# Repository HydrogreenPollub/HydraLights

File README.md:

View this project on [CADLAB.io](https://cadlab.io/project/29338). 

# HydraLights

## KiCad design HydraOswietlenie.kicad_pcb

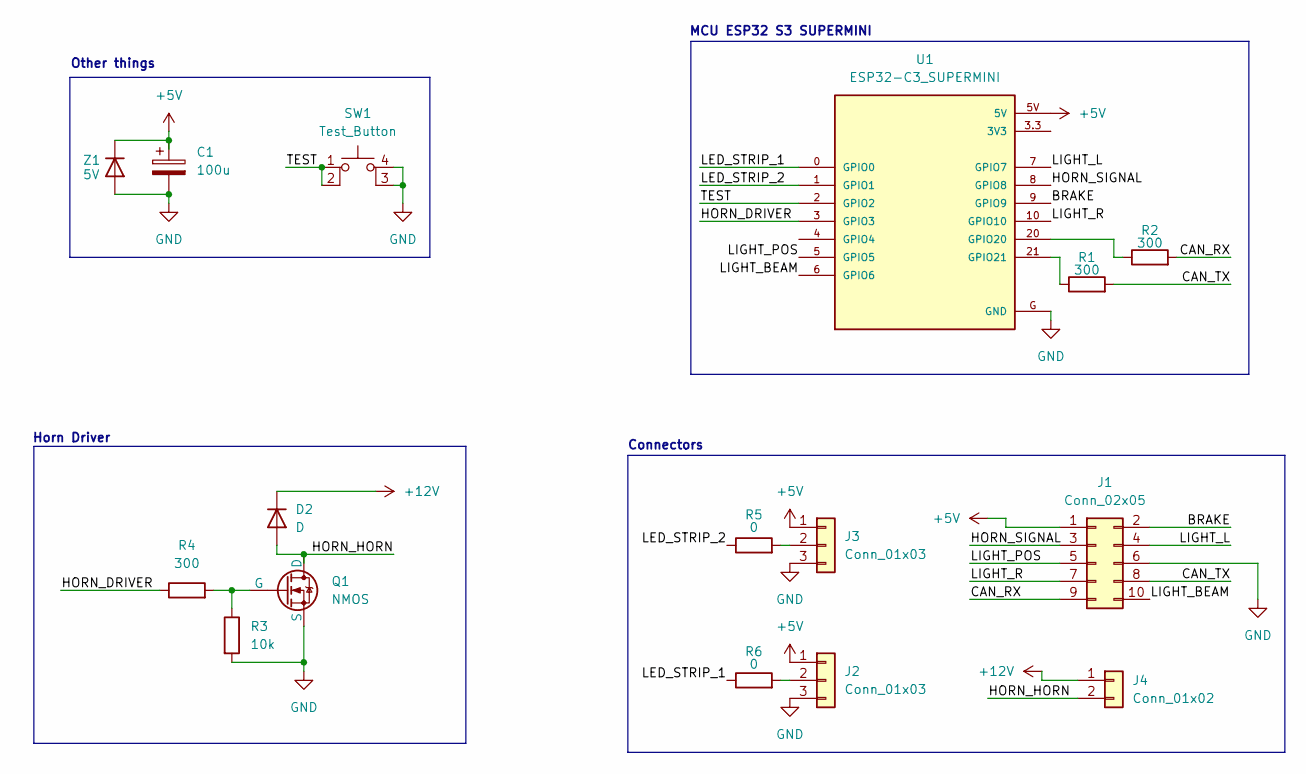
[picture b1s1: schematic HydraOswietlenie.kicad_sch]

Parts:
C1: 100u; CP_Radial_D10.0mm_P5.00mm
D2: D; D_DO-41_SOD81_P10.16mm_Horizontal
J1: Conn_02x05; Molex_Mini-Fit_Jr_5569-10A1_2x05_P4.20mm_Horizontal
J2, J3: Conn_01x03; 39303035
J4: Conn_01x02; Molex_Mini-Fit_Jr_5569-02A2_2x01_P4.20mm_Horizontal
Q1: NMOS; TO546P1558X498X2499-3
R1, R2, R4: 300; R_Axial_DIN0207_L6.3mm_D2.5mm_P7.62mm_Horizontal
R3: 10k; R_Axial_DIN0207_L6.3mm_D2.5mm_P7.62mm_Horizontal
R5, R6: 0; R_Axial_DIN0207_L6.3mm_D2.5mm_P7.62mm_Horizontal
SW1: Test_Button; TL3305BF160QG
U1: ESP32-C3_SUPERMINI; MODULE_ESP32-C3_SUPERMINI
Z1: 5V; D_DO-41_SOD81_P10.16mm_Horizontal

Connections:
+5V: C1.1, J1.1, J2.1, J3.1, U1.5V, Z1.1 (K)
+12V: D2.1 (K), J4.1
/BRAKE: J1.2, U1.9 (GPIO9)
/CAN_RX: J1.9, R2.2
/CAN_TX: J1.8, R1.2
/HORN_DRIVER: R4.1, U1.3 (GPIO3)
/HORN_HORN: D2.2 (A), J4.2, Q1.1 (D)
/HORN_SIGNAL: J1.3, U1.8 (GPIO8)
/LED_STRIP_1: R6.1, U1.0 (GPIO0)
/LED_STRIP_2: R5.1, U1.1 (GPIO1)
/LIGHT_BEAM: J1.10, U1.6 (GPIO6)
/LIGHT_L: J1.4, U1.7 (GPIO7)
/LIGHT_POS: J1.5, U1.5 (GPIO5)
/LIGHT_R: J1.7, U1.10 (GPIO10)
/TEST: SW1.1, SW1.2, U1.2 (GPIO2)
GND: C1.2, J1.6, J2.3, J3.3, Q1.3 (S), R3.2, SW1.3 (K), SW1.4 (A), U1.G (GND), Z1.2 (A); also elsewhere on the board
unnamed: J2.2, R6.2
unnamed: J3.2, R5.2
unnamed: Q1.2 (G), R3.1, R4.2
unnamed: R2.1, U1.20 (GPIO20)
unnamed: R1.1, U1.21 (GPIO21)

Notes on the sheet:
Horn Driver
Other things
MCU ESP32 S3 SUPERMINI
Connectors

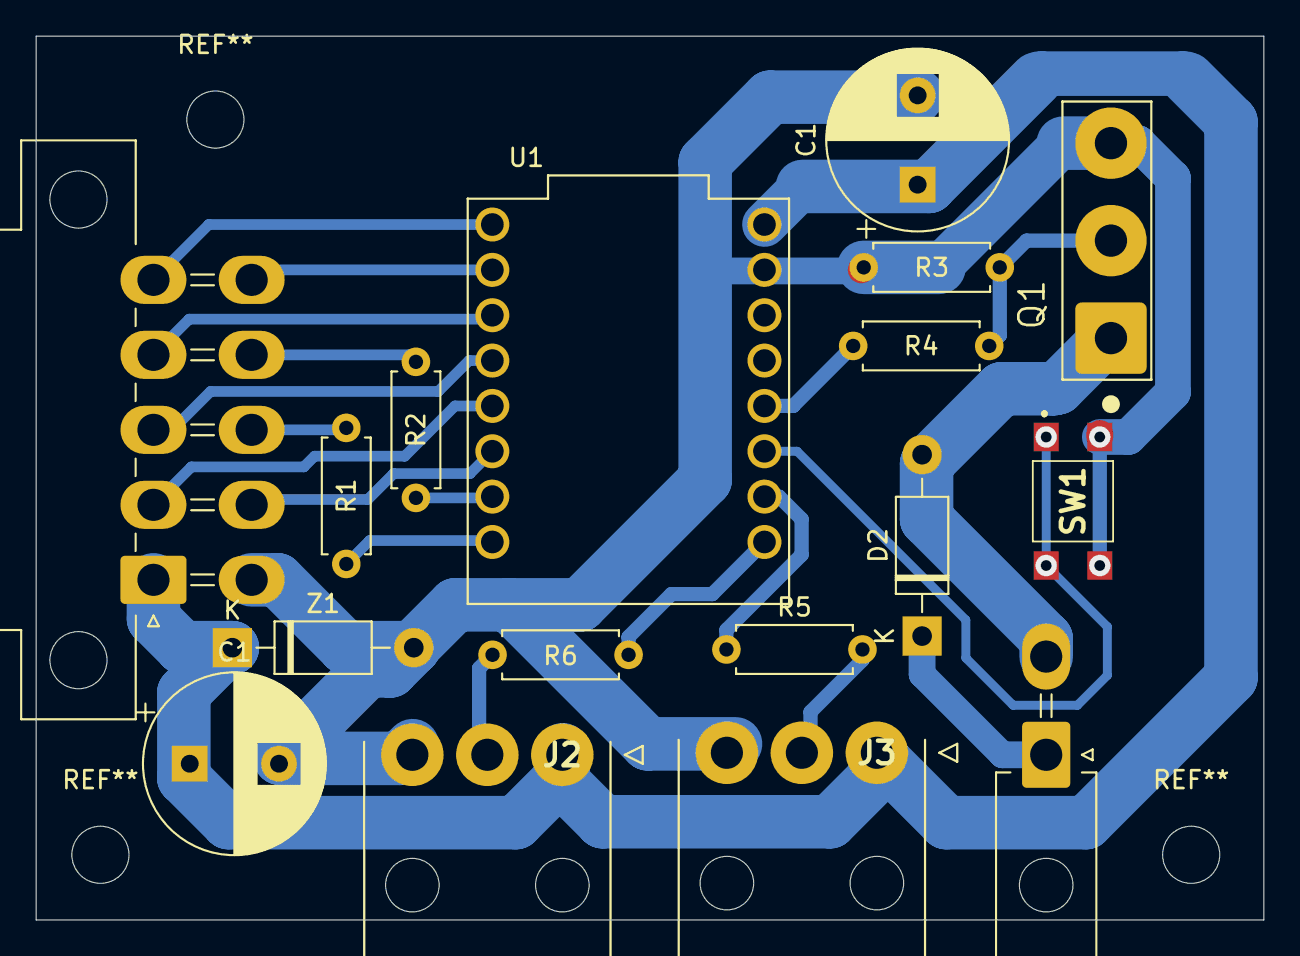
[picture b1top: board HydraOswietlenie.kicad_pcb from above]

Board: 2 copper layers, 68.8 x 49.5 mm, 17 parts (0 on the bottom side), 21 nets.

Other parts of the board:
C1#2: 100u; CP_Radial_D10.0mm_P5.00mm

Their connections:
GND: C1#2.2; also elsewhere on the board

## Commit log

2025-05-05 Update schematic
2025-05-05 Backlink to CADLAB.io has been added.
